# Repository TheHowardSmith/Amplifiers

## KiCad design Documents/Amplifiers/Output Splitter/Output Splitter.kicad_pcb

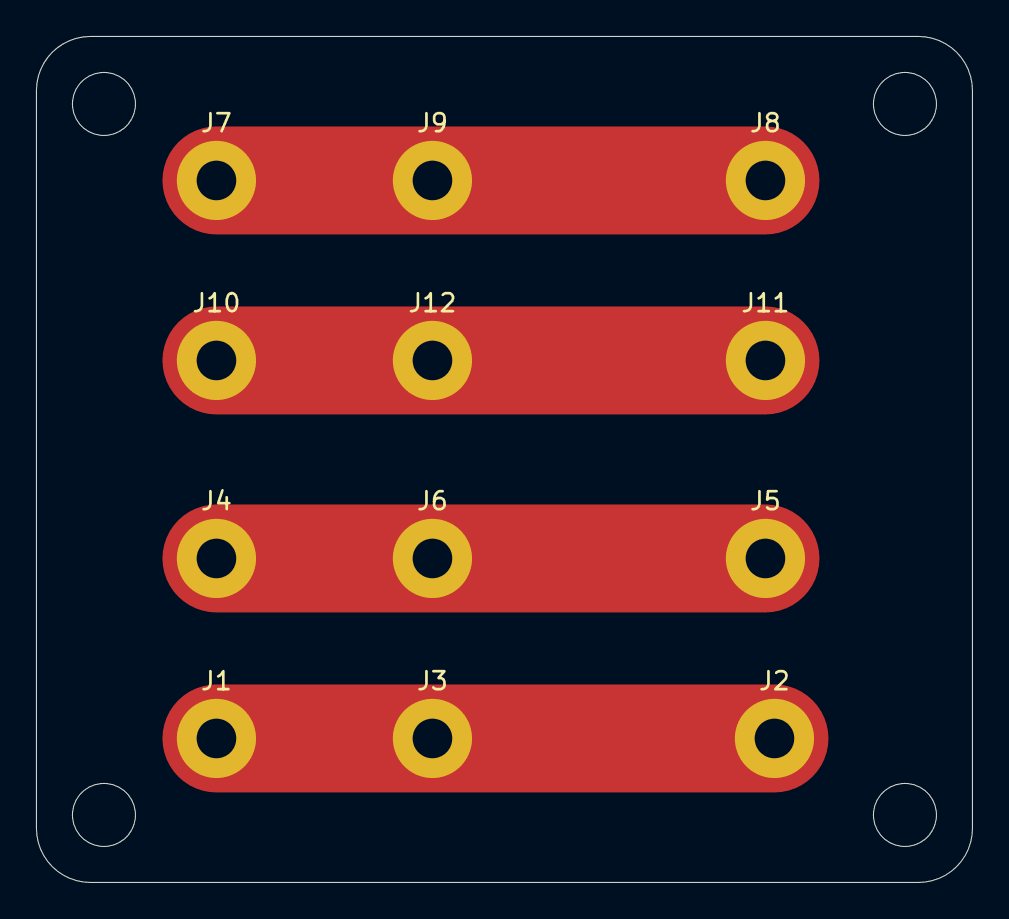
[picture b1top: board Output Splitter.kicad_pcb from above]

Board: 2 copper layers, 52.0 x 47.0 mm, 12 parts (0 on the bottom side), 4 nets.

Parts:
J1: SpeakON_Out_L; MountingHole_2.2mm_M2_Pad
J2: Amp_Out_L; MountingHole_2.2mm_M2_Pad
J3: Banana_Out_L; MountingHole_2.2mm_M2_Pad
J4: SpeakON_GND_L; MountingHole_2.2mm_M2_Pad
J5: Amp_GND_L; MountingHole_2.2mm_M2_Pad
J6: Banana_GND_L; MountingHole_2.2mm_M2_Pad
J7: SpeakON_Out_R; MountingHole_2.2mm_M2_Pad
J8: Amp_Out_R; MountingHole_2.2mm_M2_Pad
J9: Banana_Out_R; MountingHole_2.2mm_M2_Pad
J10: SpeakON_GND_R; MountingHole_2.2mm_M2_Pad
J11: Amp_GND_R; MountingHole_2.2mm_M2_Pad
J12: Banana_GND_R; MountingHole_2.2mm_M2_Pad

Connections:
unnamed: J1.1, J2.1, J3.1
unnamed: J4.1, J5.1, J6.1
unnamed: J7.1, J8.1, J9.1
unnamed: J10.1, J11.1, J12.1

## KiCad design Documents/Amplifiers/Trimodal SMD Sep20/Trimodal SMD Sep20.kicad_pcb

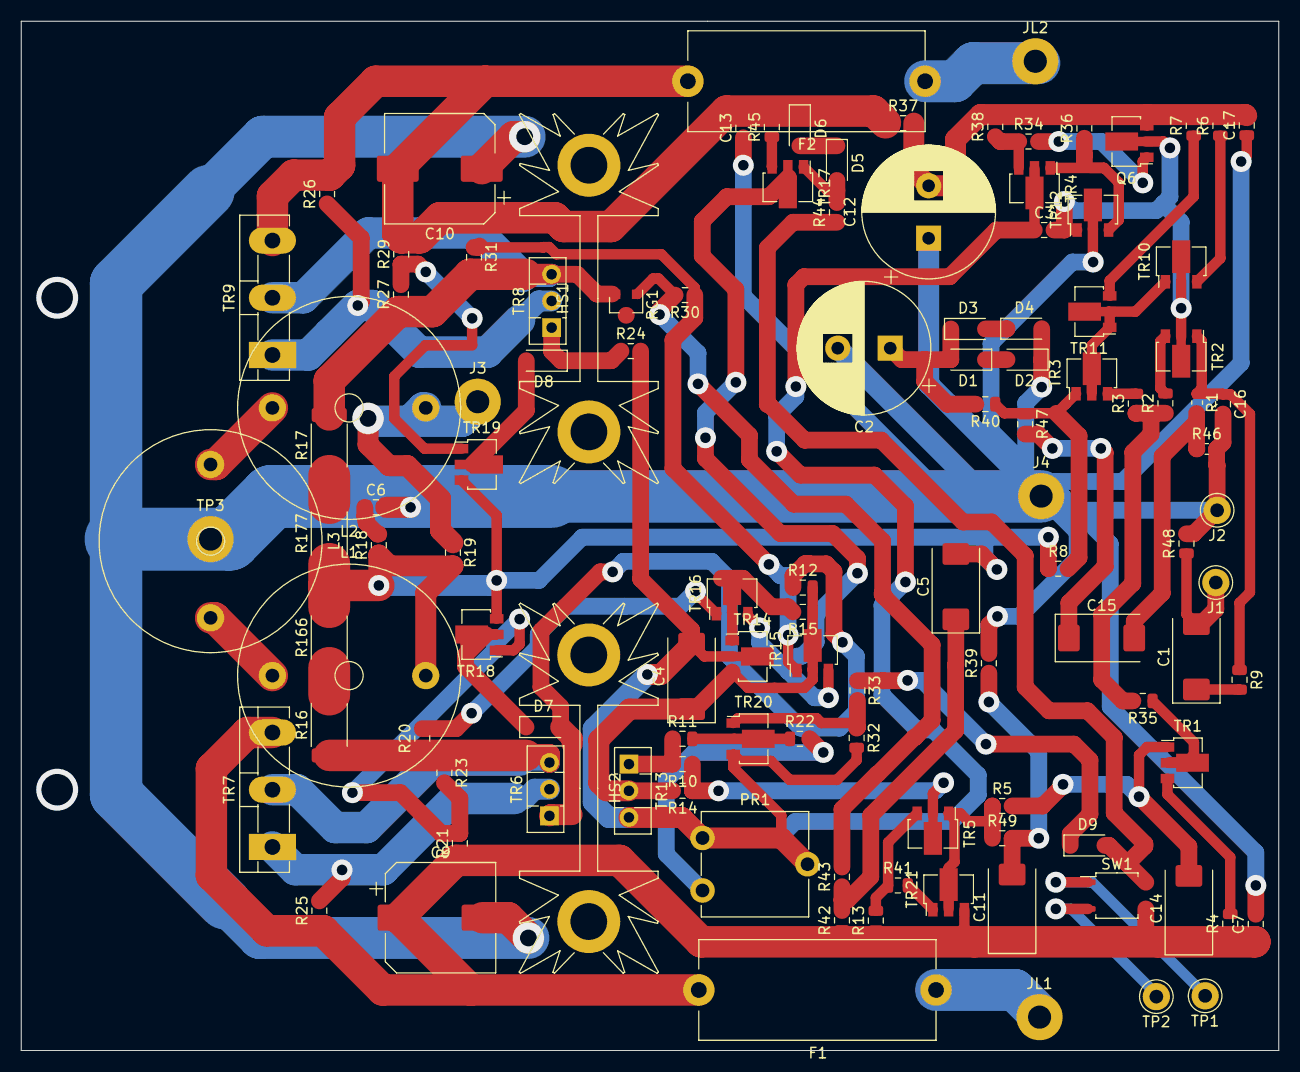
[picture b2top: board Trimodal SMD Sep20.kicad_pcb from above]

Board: 2 copper layers, 119.8 x 98.0 mm, 116 parts (0 on the bottom side), 65 nets.

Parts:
C1, C4, C5, C11, C14, C15: 47/25; CP_EIA-7343-31_Kemet-D
C2: 1000UF; CP_Radial_D12.5mm_P5.00mm
C3, C16: 100PF; C_0805_2012Metric
C6, C7, C13, C17: 100NF; C_0805_2012Metric
C9, C10: 220UF; CP_Elec_10x10
C12: 1000/40; CP_Radial_D12.5mm_P5.00mm
D1, D2, D3, D4, D5, D6, D7, D8, D9: 1N4148; D_SOD-123
F1, F2: Fuse; Fuseholder_Cylinder-5x20mm_Stelvio-Kontek_PTF78_Horizontal_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
HS1, HS2: Heatsink; Heatsink_Fischer_SK104-STCB_35x13mm__2xDrill3.5mm_ScrewM3
J1, J2: Conn_01x01_Male; Pin_D1.3mm_L11.0mm
J3, J4: Conn_01x01_Male; MountingHole_2.2mm_M2_Pad
JL1, JL2: Conn_01x01_Female; MountingHole_2.2mm_M2_Pad
L1, L2, L3: L; L_Radial_D21.0mm_P14.61mm_Vishay_IHB-2
PR1: 1K; Potentiometer_ACP_CA9-V10_Vertical
Q6: Q_NPN_BCE; SOT-89-3
R1, R46: 1K1; R_0603_1608Metric
R2, R3, R4, R12, R22, R24, R25, R26, R47: 100R; R_0805_2012Metric
R5, R8, R15, R34, R36, R41: 2K2; R_0805_2012Metric
R6, R7, R13: 68R; R_0805_2012Metric
R9, R18, R19, R37, R38: 10R; R_0805_2012Metric
R10: 680R; R_0805_2012Metric
R11, R23, R27: 270R; R_0805_2012Metric
R14: 16R; R_0805_2012Metric
R16, R17: R075; R_2512_6332Metric
R20, R31, R35, R45: 1K; R_0805_2012Metric
R21, R29: 22K; R_0805_2012Metric
R30: 3K; R_0805_2012Metric
R32: 680K; R_0805_2012Metric
R33, R44, R48: 100K; R_0805_2012Metric
R39, R42, R43, R49: 10K; R_0805_2012Metric
R40: 110R; R_0805_2012Metric
R166, R177: R025; R_2512_6332Metric
RG1: LM385BZ-1.2; SOT-23
SW1: SW_SPST; SOP-4_3.8x4.1mm_P2.54mm
TP1, TP2: Conn_01x01_Female; Pin_D1.3mm_L11.0mm
TP3: Conn_01x01_Female; MountingHole_2.2mm_M2_Pad
TR1, TR2, TR3, TR5, TR14, TR19, TR21: Q_PNP_BCE; SOT-89-3
TR4, TR10, TR11, TR12, TR15, TR16, TR17, TR18, TR20: Q_NPN_BCE; SOT-89-3
TR6, TR13: MJE13003; TO-126-3_Vertical
TR7, TR9: 2N3055; TO-3P-3_Vertical
TR8: BCP51; TO-126-3_Vertical

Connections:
GND: C2.2, C6.2, C7.2, C9.2, C10.1, C12.1, C13.1, C16.2, C17.1, D2.1, D4.2, J2.1, J4.1, R39.2, R46.2, R48.2, TR12.2
NFB: C5.2, L1.2, R8.1, R18.1, R19.2, R166.2, R177.1, TR18.3, TR19.3
unnamed: C1.1, R9.2
unnamed: C1.2, J1.1, R48.1
unnamed: C2.1, D1.2, D3.1, R40.2
unnamed: C3.1, C4.2, PR1.2, PR1.3, R24.2, R32.2, TR4.2, TR13.3, TR14.2, TR20.3
unnamed: C3.2, Q6.2, TR2.2, TR10.2, TR12.1
unnamed: C4.1, R12.2, R14.2, R15.1, TR13.2, TR14.3, TR15.2
unnamed: C5.1, R42.2, R43.1
unnamed: C6.1, R18.2
unnamed: C11.2, R39.1, R49.2
unnamed: C12.2, C17.2, Q6.3, R6.2, R7.2, R36.2, R37.2, R38.2
unnamed: C14.2, R5.2, TR1.1
unnamed: C15.1, R47.2
unnamed: C15.2, R1.2, R46.1
unnamed: C16.1, R1.1, R9.1, TR2.1
unnamed: D1.1, D2.2
unnamed: D3.2, D4.1
unnamed: D5.1, D6.2
unnamed: D5.2, R44.2, TR17.1
unnamed: D7.1, TR18.2
unnamed: D7.2, R12.1, TR6.1
unnamed: D8.1, R24.1, TR8.1
unnamed: D8.2, TR19.2
unnamed: D9.1, R33.1
unnamed: D9.2, R44.1, SW1.2
unnamed: J3.1, L2.1, R19.1
unnamed: L1.1, L3.2
unnamed: L2.2, L3.1
unnamed: PR1.1, R22.2
unnamed: Q6.1, R34.2
unnamed: R2.1, R3.1, R35.2
unnamed: R2.2, TR2.3
unnamed: R3.2, TR3.3
unnamed: R4.2, TR1.3
unnamed: R6.1, TR10.3
unnamed: R7.1, TR11.3
unnamed: R10.1, R14.1, TR5.2
unnamed: R10.2, R11.1, TR13.1
unnamed: R11.2, R22.1, TR20.2
unnamed: R13.2, R41.1, TR5.3
unnamed: R15.2, TR14.1, TR16.2
unnamed: R16.1, R20.1, R23.1, TR6.3, TR7.2
unnamed: R16.2, R166.1
unnamed: R17.1, R177.2
unnamed: R17.2, R27.1, R31.2, RG1.3, TR8.3, TR9.2
unnamed: R20.2, TR16.1
unnamed: R21.2, R23.2, TR18.1
unnamed: R25.2, TR6.2, TR7.1
unnamed: R26.1, TR8.2, TR9.1
unnamed: R27.2, R29.1, TR19.1
unnamed: R30.1, R31.1, TR15.1
unnamed: R30.2, R43.2, RG1.2
unnamed: R32.1, R33.2, TR20.1
unnamed: R34.1, R38.1, TR4.3
unnamed: R35.1, TR1.2
unnamed: R36.1, TR4.1, TR12.3
unnamed: R8.2, R40.1, R47.1, TR3.1
unnamed: R41.2, TR21.1
unnamed: R45.1, TR17.3
unnamed: R5.1, R49.1, TR5.1, TR21.2
unnamed: TR3.2, TR10.1, TR11.1, TR11.2
unnamed: TR15.3, TR16.3, TR17.2
VAA: C7.1, C9.1, C11.1, C14.1, F1.2, R4.1, R13.1, R21.1, R25.1, R42.1, SW1.1, TR7.3, TR21.3
VCC: C10.2, C13.2, D6.1, F2.2, R26.2, R29.2, R37.1, R45.2, TR9.3

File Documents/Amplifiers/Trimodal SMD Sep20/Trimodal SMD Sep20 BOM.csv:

Comment,Designator,Footprint,LCSC
220UF,"C10,C9",Capacitor_SMD:CP_Elec_10x10,C176670
47/25,"C14,C1,C15,C11,C4,C5",Capacitor_Tantalum_SMD:CP_EIA-7343-31_Kemet-D,C7228
100PF,"C16,C3",Capacitor_SMD:C_0805_2012Metric,C1790
100NF,"C7,C17,C6,C13",Capacitor_SMD:C_0805_2012Metric,C49678
1N4148,"D3,D4,D1,D2,D9,D6,D5,D7,D8",Diode_SMD:D_SOD-123,C81598
1K1,"R1,R46",Resistor_SMD:R_0603_1608Metric,C22764
680R,R10,Resistor_SMD:R_0805_2012Metric,C17798
270R,"R11,R23,R27",Resistor_SMD:R_0805_2012Metric,C17590
16R,R14,Resistor_SMD:R_0805_2012Metric,C17491
R075,"R16,R17",Resistor_SMD:R_2512_6332Metric,C76252
R025,"R166, R177",Resistor_SMD:R_2512_6332Metric,C87219
22K,"R21,R29",Resistor_SMD:R_0805_2012Metric,C17560
3K,R30,Resistor_SMD:R_0805_2012Metric,C17661
680K,R32,Resistor_SMD:R_0805_2012Metric,C17797
1K,"R35,R45,R31,R20",Resistor_SMD:R_0805_2012Metric,C17513
100R,"R4,R2,R3,R47,R24,R12,R25,R26,R22",Resistor_SMD:R_0805_2012Metric,C17408
110R,R40,Resistor_SMD:R_0805_2012Metric,C17423
100K,"R48,R33,R44",Resistor_SMD:R_0805_2012Metric,C17407
10K,"R49,R39,R42,R43",Resistor_SMD:R_0805_2012Metric,C17414
2K2,"R5,R8,R41,R36,R34,R15",Resistor_SMD:R_0805_2012Metric,C17520
68R,"R6,R7,R13",Resistor_SMD:R_0805_2012Metric,C17802
10R,"R9,R38,R37,R18,R19",Resistor_SMD:R_0805_2012Metric,C17415
LM385M3X-1.2,RG1,Package_TO_SOT_SMD:SOT-23,C77918
SW_SPST,SW1,Package_SO:SOP-4_3.8x4.1mm_P2.54mm,C99477
Q_PNP_BCE,"TR1,TR3,TR2,TR21,TR5,TR14,TR19",Package_TO_SOT_SMD:SOT-89-3,C47787
Q_NPN_BCE,"TR10,TR11,TR20,TR4,TR12,Q6,TR15,TR16,TR18,TR17",Package_TO_SOT_SMD:SOT-89-3,C100026

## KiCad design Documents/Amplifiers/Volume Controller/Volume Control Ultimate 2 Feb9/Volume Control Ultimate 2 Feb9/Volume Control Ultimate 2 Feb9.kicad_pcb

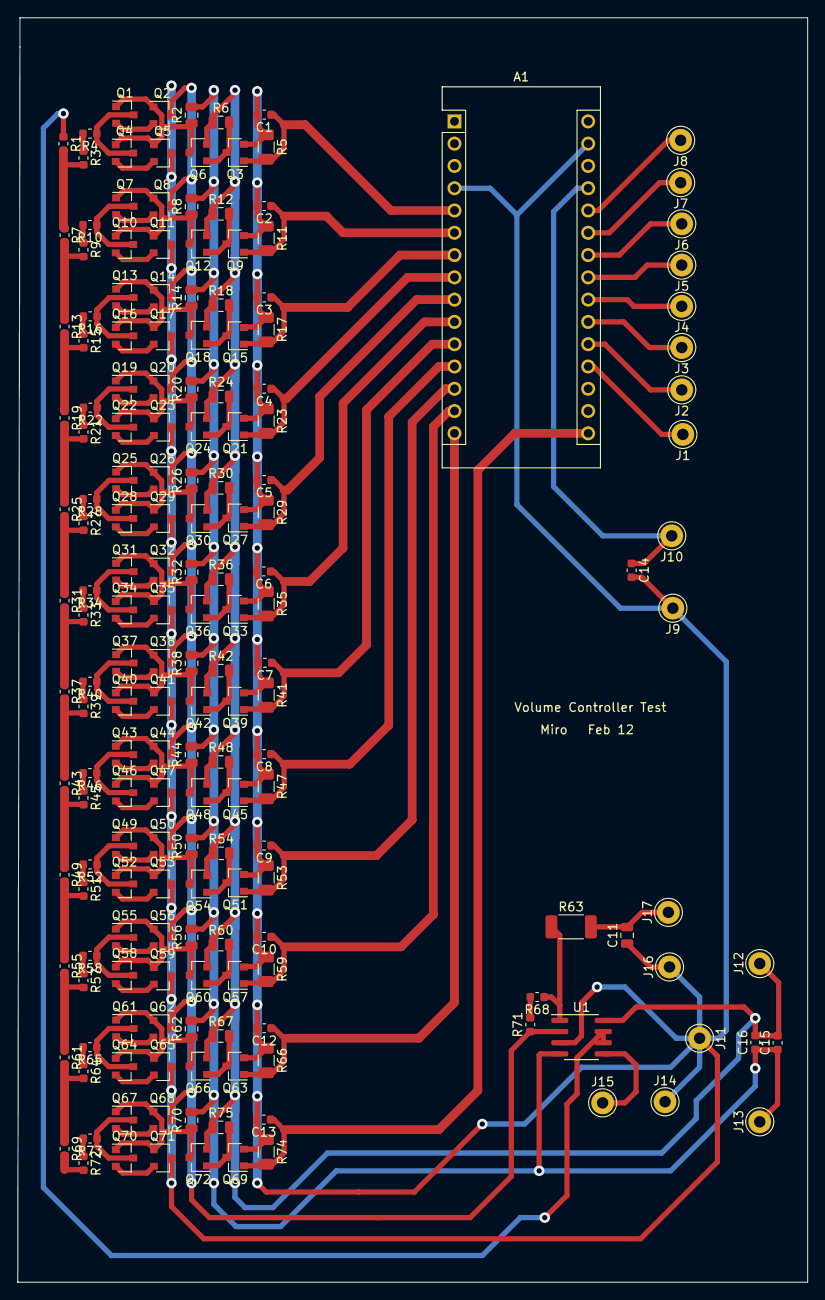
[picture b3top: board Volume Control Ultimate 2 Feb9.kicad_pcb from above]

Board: 2 copper layers, 90.0 x 144.1 mm, 182 parts (0 on the bottom side), 114 nets.

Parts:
A1: Arduino_Nano_v2.x; Arduino_Nano
C1, C2, C3, C4, C5, C6, C7, C8, C9, C10, C12, C13, C14, C15, C16: 220nF C21120; C_0603_1608Metric
C11: 10nF C1710; C_0805_2012Metric
J1: conn A0; Pin_D1.3mm_L11.0mm
J2: conn A1; Pin_D1.3mm_L11.0mm
J3: conn A2; Pin_D1.3mm_L11.0mm
J4: conn A3; Pin_D1.3mm_L11.0mm
J5: conn A4; Pin_D1.3mm_L11.0mm
J6: conn A5; Pin_D1.3mm_L11.0mm
J7: conn A6; Pin_D1.3mm_L11.0mm
J8: conn A7; Pin_D1.3mm_L11.0mm
J9: GND for Ard; Pin_D1.3mm_L11.0mm
J10: +5V for ard; Pin_D1.3mm_L11.0mm
J11: GND; Pin_D1.3mm_L11.0mm
J12: +12V; Pin_D1.3mm_L11.0mm
J13: -12V; Pin_D1.3mm_L11.0mm
J14: GND In; Pin_D1.3mm_L11.0mm
J15: In; Pin_D1.3mm_L11.0mm
J16: GND Out; Pin_D1.3mm_L11.0mm
J17: Out; Pin_D1.3mm_L11.0mm
Q1, Q2, Q3, Q7, Q8, Q9, Q13, Q14, Q15, Q19, Q20, Q21, Q25, Q26, Q27, Q31, Q32, Q33, Q37, Q38, Q39, Q43, Q44, Q45, Q49, Q50, Q51, Q55, Q56, Q57, Q61, Q62, Q63, Q67, Q68, Q69: NMOS GSD AO3400C C541722; SOT-23
Q4, Q5, Q6, Q10, Q11, Q12, Q16, Q17, Q18, Q22, Q23, Q24, Q28, Q29, Q30, Q34, Q35, Q36, Q40, Q41, Q42, Q46, Q47, Q48, Q52, Q53, Q54, Q58, Q59, Q60, Q64, Q65, Q66, Q70, Q71, Q72: PMOS GSD AO3401A C15127; SOT-23
R1, R3, R4, R7, R9, R10, R13, R15, R16, R19, R21, R22, R25, R27, R28, R31, R33, R34, R37, R39, R40, R43, R45, R46, R49, R51, R52, R55, R57, R58, R61, R64, R65, R68, R69, R71, R72, R73: 10k C128781; R_0603_1608Metric
R2, R6, R8, R12, R14, R18, R20, R24, R26, R30, R32, R36, R38, R42, R44, R48, R50, R54, R56, R60, R62, R67, R70, R75: 22k C17560; R_0805_2012Metric
R5, R11, R17, R23, R29, R35, R41, R47, R53, R59, R66, R74: 1M C17927; R_1206_3216Metric
R63: 510 Ohm C25464; R_2010_5025Metric
U1: LM833DT_Dual_Amp; SOIC-8_3.9x4.9mm_P1.27mm

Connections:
unnamed: A1.5, C1.1, Q3.1, R5.2
unnamed: A1.6, C2.1, Q9.1, R11.2
unnamed: A1.7, C3.1, Q15.1, R17.2
unnamed: A1.8, C4.1, Q21.1, R23.2
unnamed: A1.9, C5.1, Q27.1, R29.2
unnamed: A1.10, C6.1, Q33.1, R35.2
unnamed: A1.11, C7.1, Q39.1, R41.2
unnamed: A1.12, C8.1, Q45.1, R47.2
unnamed: A1.13, C9.1, Q51.1, R53.2
unnamed: A1.14, C10.1, Q57.1, R59.2
unnamed: A1.15, C12.1, Q63.1, R66.2
unnamed: A1.16, C13.1, Q69.1, R74.2
unnamed: A1.19, J1.1
unnamed: A1.20, J2.1
unnamed: A1.21, J3.1
unnamed: A1.22, J4.1
unnamed: A1.23, J5.1
unnamed: A1.24, J6.1
unnamed: A1.25, J7.1
unnamed: A1.26, J8.1
unnamed: A1.27, C14.1, J10.1
unnamed: A1.4, A1.29, C1.2, C2.2, C3.2, C4.2, C5.2, C6.2, C7.2, C8.2, C9.2, C10.2, C11.1, C12.2, C13.2, C14.2, J9.1, J11.1, J14.1, J16.1, Q3.2, Q5.3, Q9.2, Q11.3, Q15.2, Q17.3, Q21.2, Q23.3, Q27.2, Q29.3, Q33.2, Q35.3, Q39.2, Q41.3, Q45.2, Q47.3, Q51.2, Q53.3, Q57.2, Q59.3, Q63.2, Q65.3, Q69.2, Q71.3, R5.1, R11.1, R17.1, R23.1, R29.1, R35.1, R41.1, R47.1, R53.1, R59.1, R66.1, R74.1, U1.3
unnamed: C11.2, J17.1, R63.2
unnamed: C15.1, C16.1, J13.1, R2.2, R8.2, R14.2, R20.2, R26.2, R32.2, R38.2, R44.2, R50.2, R56.2, R62.2, R70.2, U1.4
unnamed: C15.2, C16.2, J12.1, Q6.2, Q12.2, Q18.2, Q24.2, Q30.2, Q36.2, Q42.2, Q48.2, Q54.2, Q60.2, Q66.2, Q72.2, R6.1, R12.1, R18.1, R24.1, R30.1, R36.1, R42.1, R48.1, R54.1, R60.1, R67.1, R75.1, U1.8
unnamed: J15.1, U1.5
unnamed: Q1.1, Q2.1, Q4.1, Q5.1, Q6.3, R2.1
unnamed: Q1.2, Q2.2
unnamed: Q1.3, Q4.3, R4.1
unnamed: Q3.3, Q6.1, R6.2
unnamed: Q4.2, Q5.2
unnamed: Q7.2, Q8.2
unnamed: Q7.1, Q8.1, Q10.1, Q11.1, Q12.3, R8.1
unnamed: Q10.2, Q11.2
unnamed: Q7.3, Q10.3, R10.1
unnamed: Q9.3, Q12.1, R12.2
unnamed: Q13.1, Q14.1, Q16.1, Q17.1, Q18.3, R14.1
unnamed: Q13.2, Q14.2
unnamed: Q13.3, Q16.3, R16.1
unnamed: Q2.3, Q8.3, Q14.3, Q20.3, Q26.3, Q32.3, Q38.3, Q44.3, Q50.3, Q56.3, Q62.3, Q68.3, R71.1, U1.2
unnamed: Q15.3, Q18.1, R18.2
unnamed: Q16.2, Q17.2
unnamed: Q19.1, Q20.1, Q22.1, Q23.1, Q24.3, R20.1
unnamed: Q19.2, Q20.2
unnamed: Q19.3, Q22.3, R22.1
unnamed: Q21.3, Q24.1, R24.2
unnamed: Q22.2, Q23.2
unnamed: Q25.1, Q26.1, Q28.1, Q29.1, Q30.3, R26.1
unnamed: Q25.2, Q26.2
unnamed: Q25.3, Q28.3, R28.1
unnamed: Q27.3, Q30.1, R30.2
unnamed: Q28.2, Q29.2
unnamed: Q31.1, Q32.1, Q34.1, Q35.1, Q36.3, R32.1
unnamed: Q31.2, Q32.2
unnamed: Q31.3, Q34.3, R34.1
unnamed: Q33.3, Q36.1, R36.2
unnamed: Q34.2, Q35.2
unnamed: Q37.1, Q38.1, Q40.1, Q41.1, Q42.3, R38.1
unnamed: Q37.2, Q38.2
unnamed: Q37.3, Q40.3, R40.1
unnamed: Q39.3, Q42.1, R42.2
unnamed: Q40.2, Q41.2
unnamed: Q43.1, Q44.1, Q46.1, Q47.1, Q48.3, R44.1
unnamed: Q43.2, Q44.2
unnamed: Q43.3, Q46.3, R46.1
unnamed: Q45.3, Q48.1, R48.2
unnamed: Q46.2, Q47.2
unnamed: Q49.1, Q50.1, Q52.1, Q53.1, Q54.3, R50.1
unnamed: Q49.2, Q50.2
unnamed: Q49.3, Q52.3, R52.1
unnamed: Q51.3, Q54.1, R54.2
unnamed: Q52.2, Q53.2
unnamed: Q55.1, Q56.1, Q58.1, Q59.1, Q60.3, R56.1
unnamed: Q55.2, Q56.2
unnamed: Q55.3, Q58.3, R58.1
unnamed: Q57.3, Q60.1, R60.2
unnamed: Q58.2, Q59.2
unnamed: Q61.1, Q62.1, Q64.1, Q65.1, Q66.3, R62.1
unnamed: Q61.2, Q62.2
unnamed: Q61.3, Q64.3, R65.1
unnamed: Q63.3, Q66.1, R67.2
unnamed: Q64.2, Q65.2
unnamed: Q67.1, Q68.1, Q70.1, Q71.1, Q72.3, R70.1
unnamed: Q67.2, Q68.2
unnamed: Q67.3, Q70.3, R73.1
unnamed: Q69.3, Q72.1, R75.2
unnamed: Q70.2, Q71.2
unnamed: R1.1, U1.6, U1.7
unnamed: R1.2, R3.2, R7.1
unnamed: R3.1, R4.2
unnamed: R9.1, R10.2
unnamed: R7.2, R9.2, R13.1
unnamed: R13.2, R15.2, R19.1
unnamed: R15.1, R16.2
unnamed: R19.2, R21.2, R25.1
unnamed: R21.1, R22.2
unnamed: R25.2, R27.2, R31.1
unnamed: R27.1, R28.2
unnamed: R31.2, R33.2, R37.1
unnamed: R33.1, R34.2
unnamed: R37.2, R39.2, R43.1
unnamed: R39.1, R40.2
unnamed: R43.2, R45.2, R49.1
unnamed: R45.1, R46.2
unnamed: R49.2, R51.2, R55.1
unnamed: R51.1, R52.2
unnamed: R55.2, R57.2, R61.1
unnamed: R57.1, R58.2
unnamed: R61.2, R64.2, R69.1
unnamed: R63.1, R68.1, U1.1
unnamed: R64.1, R65.2
unnamed: R68.2, R71.2
unnamed: R69.2, R72.2
unnamed: R72.1, R73.2

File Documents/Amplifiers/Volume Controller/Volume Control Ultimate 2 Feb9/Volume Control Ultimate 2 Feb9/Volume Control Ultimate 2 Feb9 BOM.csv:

Comment,Designator,Footprint,LCSC
220nF,"C1,C2,C3,C4,C5,C6,C7,C8,C9,C10,C12,C13,C15,C16,C14",Capacitor_SMD:C_0603_1608Metric,C21120
10nF,C11,Capacitor_SMD:C_0805_2012Metric,C1710
NMOS GSD AO3400A,"Q68,Q69,Q67,Q62,Q63,Q61,Q56,Q57,Q55,Q50,Q51,Q49,Q44,Q45,Q43,Q38,Q39,Q37,Q32,Q33,Q31,Q26,Q27,Q25,Q20,Q21,Q19,Q14,Q15,Q13,Q8,Q9,Q7,Q2,Q3,Q1",Package_TO_SOT_SMD:SOT-23,C347475
PMOS GSD AO3401A,"Q72,Q71,Q70,Q66,Q65,Q64,Q60,Q59,Q58,Q54,Q53,Q52,Q48,Q47,Q46,Q42,Q41,Q40,Q36,Q35,Q34,Q30,Q29,Q28,Q24,Q23,Q22,Q18,Q17,Q16,Q12,Q11,Q10,Q6,Q5,Q4",Package_TO_SOT_SMD:SOT-23,C15127
1M,"R5,R11,R17,R23,R29,R35,R41,R47,R53,R59,R66,R74",Resistor_SMD:R_1206_3216Metric,C17927
510 Ohm,R63,Resistor_SMD:R_2010_5025Metric,C25464
22k,"R70,R75,R62,R67,R56,R60,R50,R54,R44,R48,R38,R42,R32,R36,R26,R30,R20,R24,R14,R18,R8,R12,R2,R6",Resistor_SMD:R_0805_2012Metric,C17560
10k,"R72,R73,R69,R64,R65,R61,R57,R58,R55,R51,R52,R49,R45,R46,R43,R39,R40,R37,R33,R34,R31,R27,R28,R25,R21,R22,R19,R15,R16,R13,R9,R10,R7,R3,R4,R1,R68,R71",Resistor_SMD:R_0603_1608Metric,C128781
LM833DT_Dual_Amp,U1,Package_SO:SOIC-8_3.9x4.9mm_P1.27mm,C127074

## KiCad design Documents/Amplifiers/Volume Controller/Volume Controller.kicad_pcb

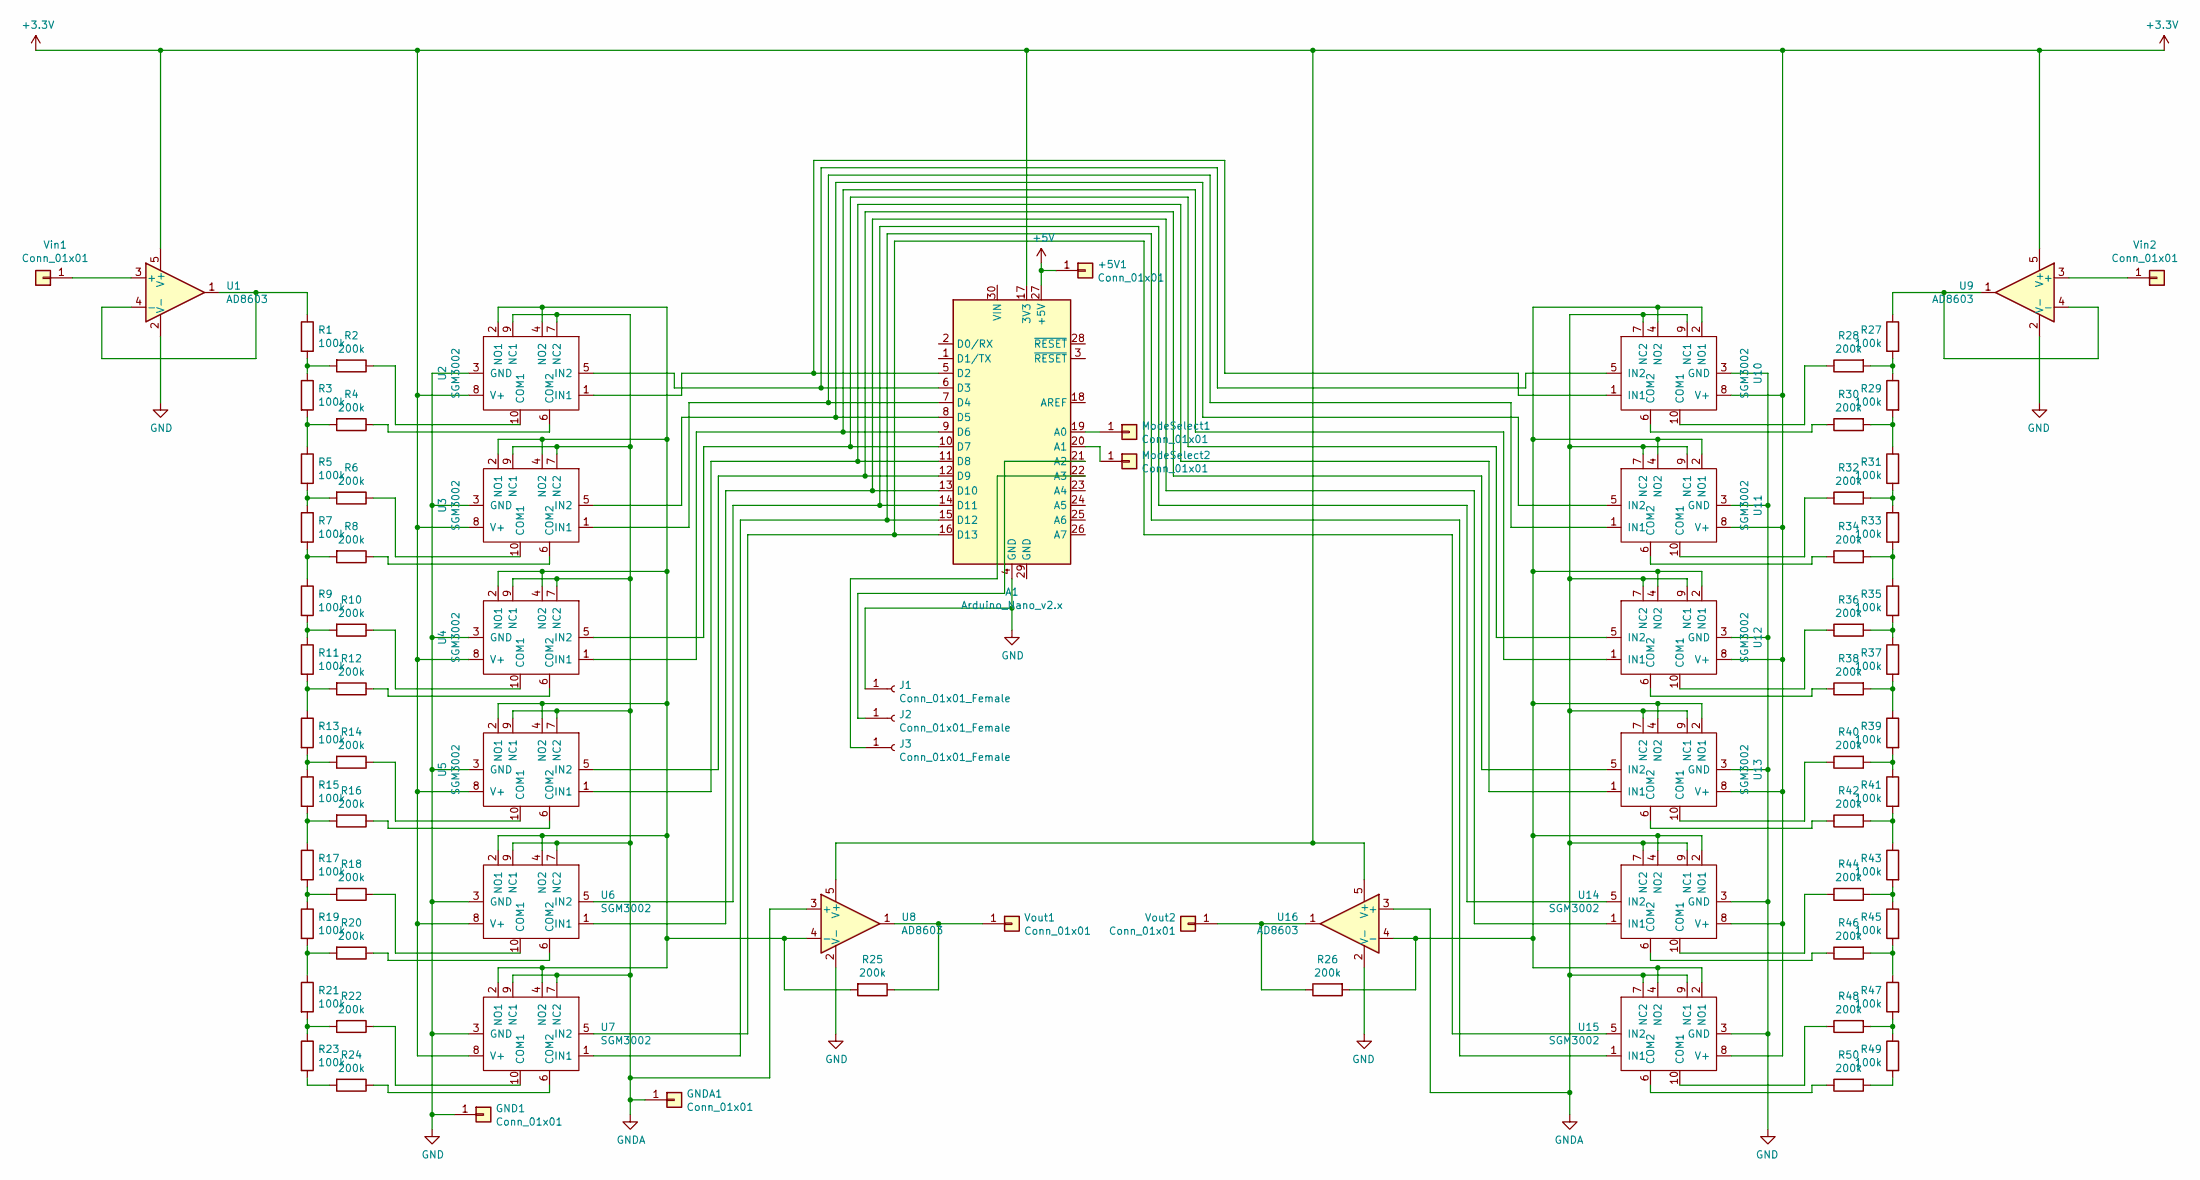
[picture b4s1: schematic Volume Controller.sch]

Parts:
+5V1: Conn_01x01; Pin_D1.3mm_L11.0mm
A1: Arduino_Nano_v2.x; Arduino_Nano
GND1: Conn_01x01; Pin_D1.3mm_L11.0mm
GNDA1: Conn_01x01; Pin_D1.3mm_L11.0mm
J1, J2, J3: Conn_01x01_Female; Pin_D1.3mm_L11.0mm
ModeSelect1, ModeSelect2: Conn_01x01; Pin_D1.3mm_L11.0mm
R1, R3, R5, R7, R9, R11, R13, R15, R17, R19, R21, R23, R27, R29, R31, R33, R35, R37, R39, R41, R43, R45, R47, R49: 100k; R_1206_3216Metric
R2, R4, R6, R8, R10, R12, R14, R16, R18, R20, R22, R24, R25, R26, R28, R30, R32, R34, R36, R38, R40, R42, R44, R46, R48, R50: 200k; R_0805_2012Metric
U1, U8, U9, U16: AD8603; TSOT-23-5
U2, U3, U4, U5, U6, U7, U10, U11, U12, U13, U14, U15: SGM3002; MSOP-10_3x3mm_P0.5mm
Vin1, Vin2: Conn_01x01; Pin_D1.3mm_L11.0mm
Vout1, Vout2: Conn_01x01; Pin_D1.3mm_L11.0mm

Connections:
+3V3: A1.17 (3V3), U1.5 (V+), U2.8 (V+), U3.8 (V+), U4.8 (V+), U5.8 (V+), U6.8 (V+), U7.8 (V+), U8.5 (V+), U9.5 (V+), U10.8 (V+), U11.8 (V+), U12.8 (V+), U13.8 (V+), U14.8 (V+), U15.8 (V+), U16.5 (V+)
+5V: +5V1.1, A1.27 (+5V)
GND: A1.4 (GND), GND1.1, J1.1, U1.2 (V-), U2.3 (GND), U3.3 (GND), U4.3 (GND), U5.3 (GND), U6.3 (GND), U7.3 (GND), U8.2 (V-), U9.2 (V-), U10.3 (GND), U11.3 (GND), U12.3 (GND), U13.3 (GND), U14.3 (GND), U15.3 (GND), U16.2 (V-)
GNDA: GNDA1.1, U2.7 (NC2), U2.9 (NC1), U3.7 (NC2), U3.9 (NC1), U4.7 (NC2), U4.9 (NC1), U5.7 (NC2), U5.9 (NC1), U6.7 (NC2), U6.9 (NC1), U7.7 (NC2), U7.9 (NC1), U8.3 (+), U10.7 (NC2), U10.9 (NC1), U11.7 (NC2), U11.9 (NC1), U12.7 (NC2), U12.9 (NC1), U13.7 (NC2), U13.9 (NC1), U14.7 (NC2), U14.9 (NC1), U15.7 (NC2), U15.9 (NC1), U16.3 (+)
unnamed: A1.5 (D2), U2.1 (IN1), U10.1 (IN1)
unnamed: A1.6 (D3), U2.5 (IN2), U10.5 (IN2)
unnamed: A1.7 (D4), U3.1 (IN1), U11.1 (IN1)
unnamed: A1.8 (D5), U3.5 (IN2), U11.5 (IN2)
unnamed: A1.9 (D6), U4.1 (IN1), U12.1 (IN1)
unnamed: A1.10 (D7), U4.5 (IN2), U12.5 (IN2)
unnamed: A1.11 (D8), U5.1 (IN1), U13.1 (IN1)
unnamed: A1.12 (D9), U5.5 (IN2), U13.5 (IN2)
unnamed: A1.13 (D10), U6.1 (IN1), U14.1 (IN1)
unnamed: A1.14 (D11), U6.5 (IN2), U14.5 (IN2)
unnamed: A1.15 (D12), U7.1 (IN1), U15.1 (IN1)
unnamed: A1.16 (D13), U7.5 (IN2), U15.5 (IN2)
unnamed: A1.19 (A0), ModeSelect1.1
unnamed: A1.20 (A1), ModeSelect2.1
unnamed: A1.21 (A2), J2.1
unnamed: A1.22 (A3), J3.1
unnamed: R1.1, U1.1, U1.4 (-)
unnamed: R1.2, R2.2, R3.1
unnamed: R2.1, U2.10 (COM1)
unnamed: R3.2, R4.2, R5.1
unnamed: R4.1, U2.6 (COM2)
unnamed: R5.2, R6.2, R7.1
unnamed: R6.1, U3.10 (COM1)
unnamed: R7.2, R8.2, R9.1
unnamed: R8.1, U3.6 (COM2)
unnamed: R10.1, U4.10 (COM1)
unnamed: R9.2, R10.2, R11.1
unnamed: R11.2, R12.2, R13.1
unnamed: R12.1, U4.6 (COM2)
unnamed: R13.2, R14.2, R15.1
unnamed: R14.1, U5.10 (COM1)
unnamed: R15.2, R16.2, R17.1
unnamed: R16.1, U5.6 (COM2)
unnamed: R17.2, R18.2, R19.1
unnamed: R18.1, U6.10 (COM1)
unnamed: R19.2, R20.2, R21.1
unnamed: R20.1, U6.6 (COM2)
unnamed: R21.2, R22.2, R23.1
unnamed: R22.1, U7.10 (COM1)
unnamed: R23.2, R24.2
unnamed: R24.1, U7.6 (COM2)
unnamed: R25.1, U8.1, Vout1.1
unnamed: R25.2, U2.2 (NO1), U2.4 (NO2), U3.2 (NO1), U3.4 (NO2), U4.2 (NO1), U4.4 (NO2), U5.2 (NO1), U5.4 (NO2), U6.2 (NO1), U6.4 (NO2), U7.2 (NO1), U7.4 (NO2), U8.4 (-)
unnamed: R26.1, U16.1, Vout2.1
unnamed: R26.2, U10.2 (NO1), U10.4 (NO2), U11.2 (NO1), U11.4 (NO2), U12.2 (NO1), U12.4 (NO2), U13.2 (NO1), U13.4 (NO2), U14.2 (NO1), U14.4 (NO2), U15.2 (NO1), U15.4 (NO2), U16.4 (-)
unnamed: R27.1, U9.1, U9.4 (-)
unnamed: R27.2, R28.2, R29.1
unnamed: R28.1, U10.10 (COM1)
unnamed: R29.2, R30.2, R31.1
unnamed: R30.1, U10.6 (COM2)
unnamed: R31.2, R32.2, R33.1
unnamed: R32.1, U11.10 (COM1)
unnamed: R33.2, R34.2, R35.1
unnamed: R34.1, U11.6 (COM2)
unnamed: R35.2, R36.2, R37.1
unnamed: R36.1, U12.10 (COM1)
unnamed: R37.2, R38.2, R39.1
unnamed: R38.1, U12.6 (COM2)
unnamed: R39.2, R40.2, R41.1
unnamed: R40.1, U13.10 (COM1)
unnamed: R41.2, R42.2, R43.1
unnamed: R42.1, U13.6 (COM2)
unnamed: R43.2, R44.2, R45.1
unnamed: R44.1, U14.10 (COM1)
unnamed: R45.2, R46.2, R47.1
unnamed: R46.1, U14.6 (COM2)
unnamed: R47.2, R48.2, R49.1
unnamed: R48.1, U15.10 (COM1)
unnamed: R49.2, R50.2
unnamed: R50.1, U15.6 (COM2)
unnamed: U1.3 (+), Vin1.1
unnamed: U9.3 (+), Vin2.1

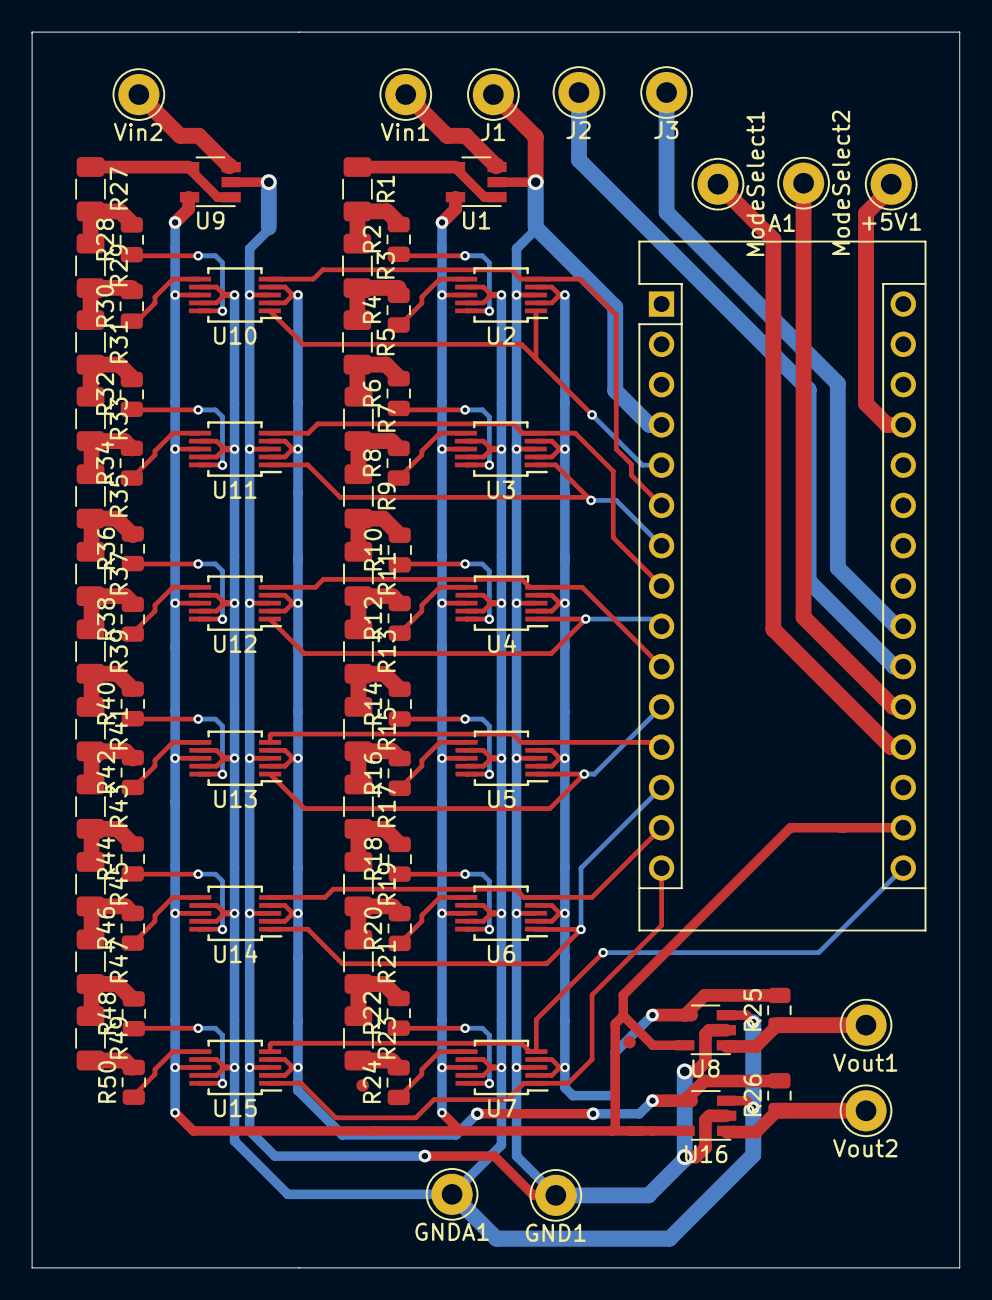
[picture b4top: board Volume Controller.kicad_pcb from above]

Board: 2 copper layers, 58.5 x 77.9 mm, 79 parts (0 on the bottom side), 76 nets.

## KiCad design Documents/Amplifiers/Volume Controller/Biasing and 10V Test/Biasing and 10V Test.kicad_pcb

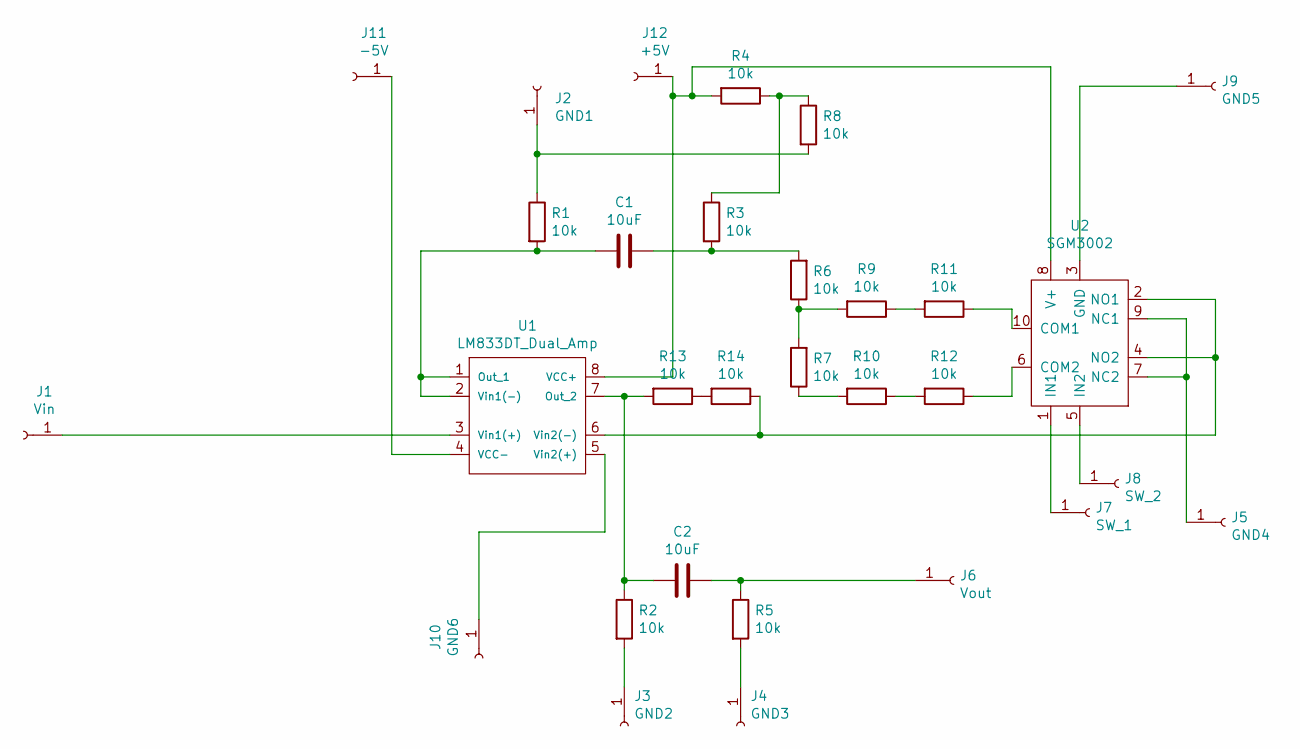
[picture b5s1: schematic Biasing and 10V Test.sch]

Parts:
C1, C2: 10uF; C_1206_3216Metric
J1: Vin; Pin_D1.3mm_L11.0mm
J2: GND1; Pin_D1.3mm_L11.0mm
J3: GND2; Pin_D1.3mm_L11.0mm
J4: GND3; Pin_D1.3mm_L11.0mm
J5: GND4; Pin_D1.3mm_L11.0mm
J6: Vout; Pin_D1.3mm_L11.0mm
J7: SW_1; Pin_D1.3mm_L11.0mm
J8: SW_2; Pin_D1.3mm_L11.0mm
J9: GND5; Pin_D1.3mm_L11.0mm
J10: GND6; Pin_D1.3mm_L11.0mm
J11: -5V; Pin_D1.3mm_L11.0mm
J12: +5V; Pin_D1.3mm_L11.0mm
R1, R2, R3, R4, R5, R6, R7, R8, R9, R10, R11, R12, R13, R14: 10k; R_1206_3216Metric
U1: LM833DT_Dual_Amp; SOIC127P600X175-8N
U2: SGM3002; MSOP-10_3x3mm_P0.5mm

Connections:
unnamed: C1.1, R3.2, R6.2
unnamed: C1.2, R1.2, U1.1 (Out_1), U1.2 (Vin1(-))
unnamed: C2.1, J6.1, R5.1
unnamed: C2.2, R2.1, R13.2, U1.7 (Out_2)
unnamed: J1.1, U1.3 (Vin1(+))
unnamed: J2.1, R1.1, R8.2
unnamed: J3.1, R2.2
unnamed: J4.1, R5.2
unnamed: J5.1, U2.7 (NC2), U2.9 (NC1)
unnamed: J7.1, U2.1 (IN1)
unnamed: J8.1, U2.5 (IN2)
unnamed: J9.1, U2.3 (GND)
unnamed: J10.1, U1.5 (Vin2(+))
unnamed: J11.1, U1.4 (VCC-)
unnamed: J12.1, R4.2, U1.8 (VCC+), U2.8 (V+)
unnamed: R3.1, R4.1, R8.1
unnamed: R6.1, R7.2, R9.2
unnamed: R10.1, R12.2
unnamed: R7.1, R10.2
unnamed: R11.1, U2.10 (COM1)
unnamed: R9.1, R11.2
unnamed: R12.1, U2.6 (COM2)
unnamed: R13.1, R14.2
unnamed: R14.1, U1.6 (Vin2(-)), U2.2 (NO1), U2.4 (NO2)

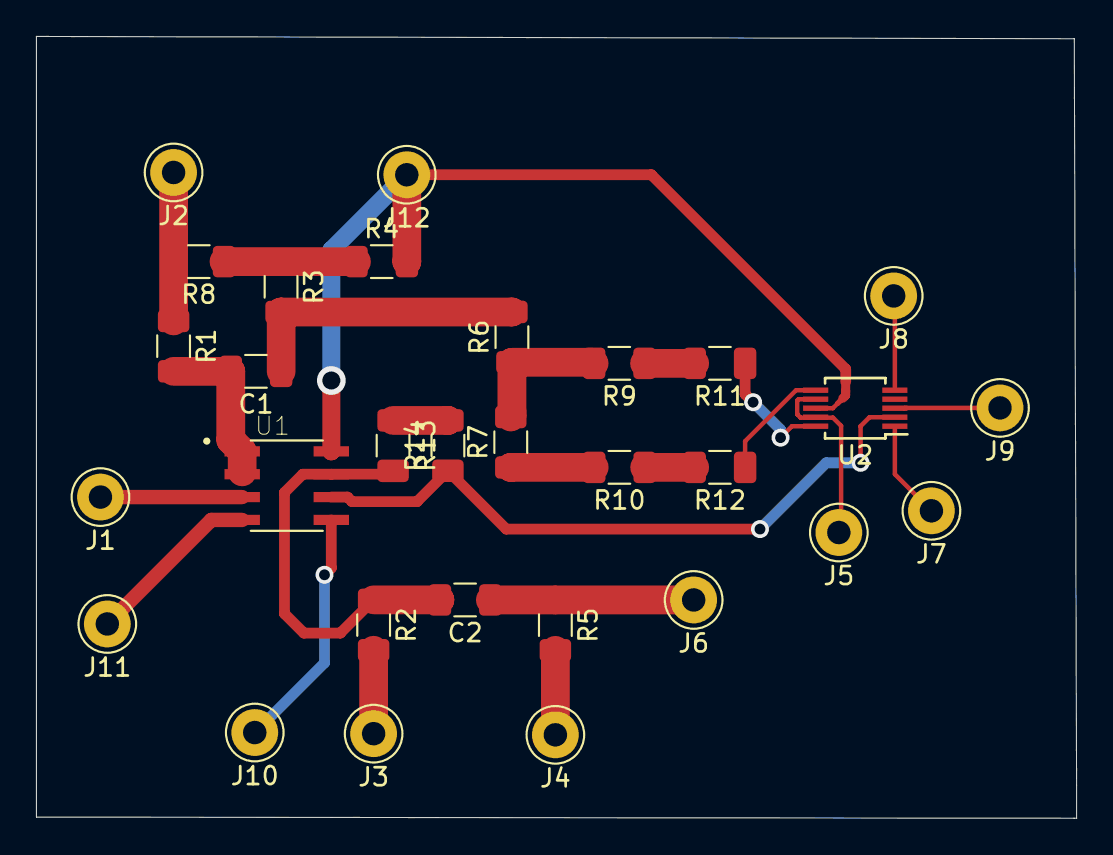
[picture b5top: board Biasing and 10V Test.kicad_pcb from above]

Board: 2 copper layers, 57.8 x 43.4 mm, 30 parts (0 on the bottom side), 24 nets.

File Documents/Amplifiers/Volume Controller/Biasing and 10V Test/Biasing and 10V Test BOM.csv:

Comment,Designator,Footprint,LCSC
10uF,"C1,C2",Capacitor_SMD:C_1206_3216Metric,C13585
10k,"R1,R3,R4,R8,R6,R9,R7,R10,R2,R5,R11,R12,R13,R14",Resistor_SMD:R_1206_3216Metric,C17902
LM833DT_Dual_Amp,U1,New symbols and footprints:SOIC127P600X175-8N,C127074
SGM3002,U2,Package_SO:MSOP-10_3x3mm_P0.5mm,C79908

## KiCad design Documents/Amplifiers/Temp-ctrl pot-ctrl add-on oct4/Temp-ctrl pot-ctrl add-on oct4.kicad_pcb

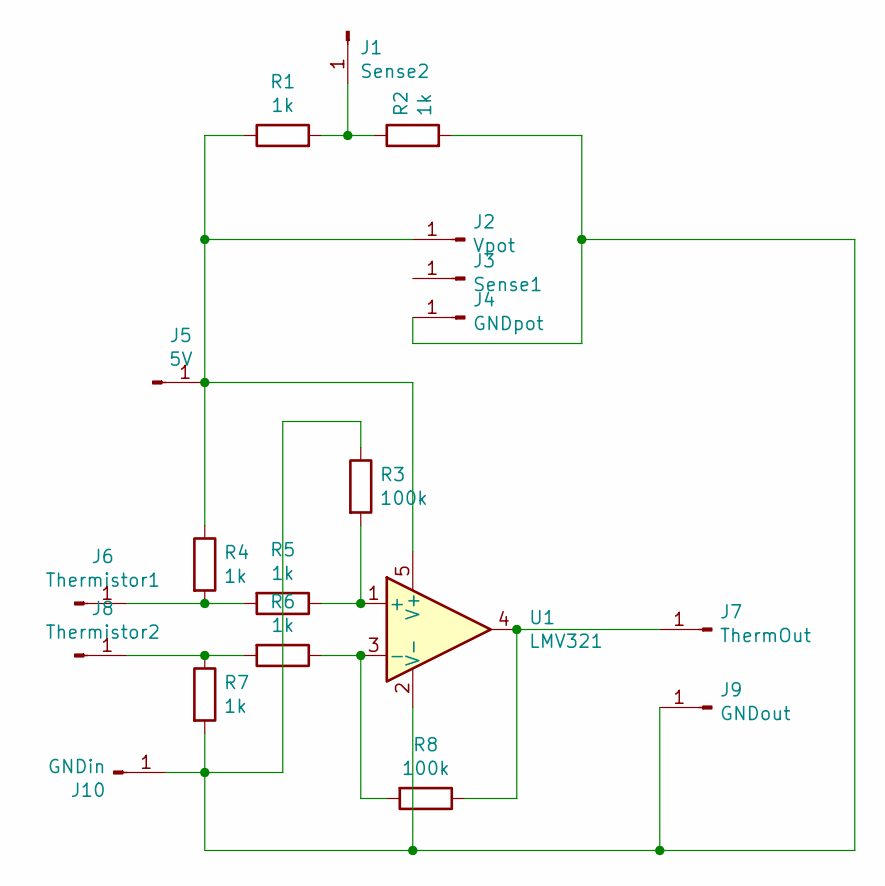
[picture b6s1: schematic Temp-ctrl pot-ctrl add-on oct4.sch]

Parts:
J1: Sense2; Pin_D1.3mm_L11.0mm
J2: Vpot; Pin_D1.3mm_L11.0mm
J3: Sense1; Pin_D1.3mm_L11.0mm
J4: GNDpot; Pin_D1.3mm_L11.0mm
J5: 5V; Pin_D1.3mm_L11.0mm
J6: Thermistor1; Molex_KK-254_AE-6410-03A_1x03_P2.54mm_Vertical
J7: ThermOut; Pin_D1.3mm_L11.0mm
J8: Thermistor2; Molex_KK-254_AE-6410-03A_1x03_P2.54mm_Vertical
J9: GNDout; Pin_D1.3mm_L11.0mm
J10: GNDin; Pin_D1.3mm_L11.0mm
R1, R2, R4, R5, R6, R7: 1k; R_0805_2012Metric
R3, R8: 100k; R_0805_2012Metric
U1: LMV321; SOT-23-5

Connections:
unnamed: J1.1, R1.2, R2.1
unnamed: J2.1, J5.1, R1.1, R4.1, U1.5 (V+)
unnamed: J6.1, R4.2, R5.2
unnamed: J7.1, R8.1, U1.4
unnamed: J8.1, R6.2, R7.1
unnamed: J4.1, J9.1, J10.1, R2.2, R3.1, R7.2, U1.2 (V-)
unnamed: R3.2, R5.1, U1.1 (+)
unnamed: R6.1, R8.2, U1.3 (-)
